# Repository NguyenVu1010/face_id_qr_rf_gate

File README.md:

# smart_gate (Pi 5 side)

See `docs/superpowers/specs/2026-05-22-pi-app-design.md` for design.

## Dev setup

```
python3 -m venv --system-site-packages .venv
source .venv/bin/activate
pip install -r requirements-dev.txt
pytest tests/ -q
```

## Production install

```
sudo bash scripts/install.sh
```

## Pi GPIO UART setup (one-time, before first run)

The daemon talks to ESP32 over the Pi GPIO UART (`/dev/serial0`), not USB-CDC.
Before first run:

1. Disable Pi serial console:
   ```
   sudo raspi-config
   # Interface Options → Serial Port
   #   "Login shell over serial?" → NO
   #   "Serial port hardware enabled?" → YES
   sudo reboot
   ```
2. Verify the device exists and is readable:
   ```
   ls -l /dev/serial0    # should be a symlink to ttyAMA0 or ttyS0
   ```
3. Wire 3 Dupont leads between Pi GPIO header and ESP32 DevKit:
   - Pi pin **8** (BCM14, TX0) → ESP32 **GPIO 32** (UART1 RX)
   - Pi pin **10** (BCM15, RX0) ← ESP32 **GPIO 25** (UART1 TX)
   - Pi pin **6** (GND) ↔ ESP32 GND

4. Add the daemon user to `dialout` so it can open `/dev/serial0`:
   ```
   sudo usermod -aG dialout smart-gate
   ```

## Flashing ESP32 (must stop daemon)

Firmware flashing still needs a separate USB cable from the Pi to the DevKit
USB-C/micro-USB port. `esptool.py` needs DTR/RTS auto-reset which the GPIO
UART doesn't provide.

```
sudo systemctl stop smart-gate
# Plug USB cable Pi → DevKit (data + power OK while daemon is stopped; the
# servo isn't moving and Pi USB current budget is plenty for the no-load case)
esptool.py --chip esp32 --port /dev/ttyUSB0 --baud 921600 write_flash 0x0 firmware.bin
# Unplug USB cable (or leave it for `pio device monitor` debug log)
sudo systemctl start smart-gate
```

After flashing, runtime traffic resumes over `/dev/serial0` (the GPIO UART).
The USB cable is optional while the daemon runs.

## Web admin smoke test (pre-merge)

With the daemon running and the ESP32 connected:

1. Open `http://<pi>:8080/`. Top bar shows green **LINK** pill + cap fps number + frame-age (< 1s). Stream `` shows a placeholder until the camera publishes.
2. Click **⏵ Open gate** — gate opens, toast "Gate opening…". Click **⏹ Close gate** — toast "Gate closing…".
3. Click **+ Tạo user mới** → confirm dialog → enroll-result card appears with QR thumbnail + ⬇ Tải QR PNG button.
4. Trigger an authorized face match — within 2 s a new row appears at the top of Recent events.
5. Watch the gate badge cycle through `idle → opening → open → timeout_warn → closing → idle` over a 20s arc; `timeout_warn` should pulse.
6. Navigate to `/events`. Toggle the `face` filter pill — only face rows show. Clear filter, choose **denied** — only stranger rows show. Type "ali" in the user search — only alice rows. Pick "Last 7 days" period. Click `▶` on a row that has a clip — native `<dialog>` modal plays the mp4 + offers Download.
7. Navigate to `/users` — alice row visible with QR thumbnail + ⬇ download button. Counter shows "N enrolled".
8. Navigate to `/system` — four status cards green (LINK / CAP / DET / DISK), pretty-printed health JSON, two diag buttons. Click **Send ping** → modal opens with `ack_ms` integer. Click **Send cmd:status** → modal updates with the ESP32-side status payload. ESP32 log scrolls live, newest-first.
9. **Failure-mode walk:**
   - Unplug USB to ESP32. Within ~5 s:
     - Top bar LINK pill turns amber.
     - `link-banner` appears: "⚠ Link down — UART silent. Manual gate commands disabled."
     - `Open gate` → toast "Gate command failed".
     - `#sse-status` becomes "reconnecting…".
   - Replug USB. Within ~5 s: banner disappears, LINK turns green, SSE pill goes live; any ESP32 log lines emitted during the outage are replayed (uses `Last-Event-ID` resume).
10. **Pause / Clear** controls on the ESP32 log list work; capacity is bounded at 500 lines (oldest dropped).

If any step fails: `pytest tests/ -q --ignore=tests/unit/test_cli.py` should still be green; the bug is in templates/JS rather than backend.

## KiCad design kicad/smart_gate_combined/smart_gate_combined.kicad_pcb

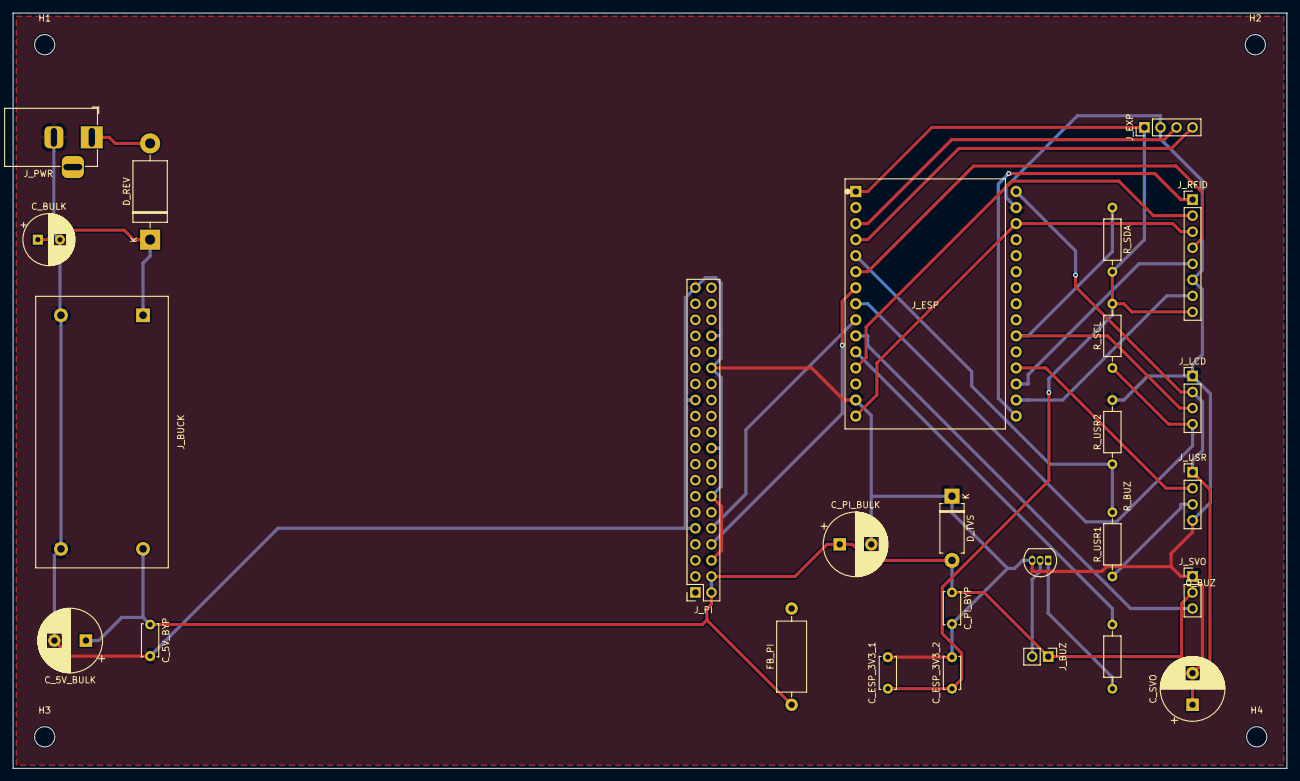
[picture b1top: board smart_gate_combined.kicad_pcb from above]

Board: 2 copper layers, 201.7 x 119.6 mm, 31 parts (0 on the bottom side), 24 nets.

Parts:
C_5V_BULK: 1000uF/10V; CP_Radial_D10.0mm_P5.00mm
C_5V_BYP: 100nF; C_Disc_D5.0mm_W2.5mm_P5.00mm
C_BULK: 100uF/25V; CP_Radial_D8.0mm_P3.50mm
C_ESP_3V3_1: 100nF; C_Disc_D5.0mm_W2.5mm_P5.00mm
C_ESP_3V3_2: 10uF; C_Disc_D5.0mm_W2.5mm_P5.00mm
C_PI_BULK: 1000uF/10V; CP_Radial_D10.0mm_P5.00mm
C_PI_BYP: 100nF; C_Disc_D5.0mm_W2.5mm_P5.00mm
C_SVO: 470uF/16V; CP_Radial_D10.0mm_P5.00mm
D_REV: 1N5817; D_DO-201AD_P15.24mm_Horizontal
D_TVS: SMAJ5.0A; D_DO-15_P10.16mm_Horizontal
FB_PI: FB_600R_3A; L_Axial_L11.0mm_D4.5mm_P15.24mm_Horizontal_Fastron_MECC
H1, H2, H3, H4: MountingHole_3.2mm_M3
J_BUCK: LM2596_Mini_Buck
J_BUZ: Buzzer_Active; PinHeader_1x02_P2.54mm_Vertical
J_ESP: ESP32_DevKit_V1; ESP32_DevKit_V1_30pin
J_EXP: Expansion; PinHeader_1x04_P2.54mm_Vertical
J_LCD: LCD_20x4_I2C; PinHeader_1x04_P2.54mm_Vertical
J_PI: Pi_5_GPIO_2x20; PinSocket_2x20_P2.54mm_Vertical
J_PWR: 12V_IN; BarrelJack_Horizontal
J_RFID: RC522; PinHeader_1x08_P2.54mm_Vertical
J_SVO: Servo_SG90; PinHeader_1x03_P2.54mm_Vertical
J_USR: HC-SR04; PinHeader_1x04_P2.54mm_Vertical
Q_BUZ: 2N3904; TO-92_Inline
R_BUZ: 1k; R_Axial_DIN0207_L6.3mm_D2.5mm_P10.16mm_Horizontal
R_SCL: 4.7k; R_Axial_DIN0207_L6.3mm_D2.5mm_P10.16mm_Horizontal
R_SDA: 4.7k; R_Axial_DIN0207_L6.3mm_D2.5mm_P10.16mm_Horizontal
R_USR1: 1k; R_Axial_DIN0207_L6.3mm_D2.5mm_P10.16mm_Horizontal
R_USR2: 2k; R_Axial_DIN0207_L6.3mm_D2.5mm_P10.16mm_Horizontal

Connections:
+3V3: C_ESP_3V3_1.1, C_ESP_3V3_2.1, J_ESP.1, J_EXP.1, J_RFID.8, R_SCL.2, R_SDA.2
+5V: C_5V_BULK.1, C_5V_BYP.1, C_PI_BULK.1, C_PI_BYP.1, C_SVO.1, D_TVS.2, FB_PI.1, J_BUCK.4, J_BUZ.1, J_ESP.2, J_LCD.2, J_PI.2, J_PI.4, J_SVO.2, J_USR.1
+12V: C_BULK.1, D_REV.1, J_BUCK.1
BUZ_COLLECTOR: J_BUZ.2, Q_BUZ.2
BUZ_DRIVE: J_ESP.21, R_BUZ.1
ESP_TX_PI_RX: J_ESP.17, J_PI.10
GND: C_5V_BULK.2, C_5V_BYP.2, C_BULK.2, C_ESP_3V3_1.2, C_ESP_3V3_2.2, C_PI_BULK.2, C_PI_BYP.2, C_SVO.2, D_TVS.1, J_BUCK.2, J_BUCK.3, J_ESP.4, J_ESP.27, J_EXP.2, J_LCD.1, J_PI.6, J_PI.9, J_PI.14, J_PI.20, J_PI.25, J_PI.30, J_PI.34, J_PI.39, J_PWR.2, J_RFID.6, J_SVO.1, J_USR.4, Q_BUZ.3, R_USR2.2
HCSR_ECHO_3V3: J_ESP.9, R_USR1.2, R_USR2.1
HCSR_ECHO_5V: J_USR.3, R_USR1.1
HCSR_TRIG: J_ESP.24, J_USR.2
I2C_SCL: J_ESP.15, J_LCD.4, R_SCL.1
I2C_SDA: J_ESP.20, J_LCD.3, R_SDA.1
IO36: J_ESP.5, J_EXP.3
IO39: J_ESP.7, J_EXP.4
unnamed: D_REV.2, J_PWR.1
unnamed: Q_BUZ.1, R_BUZ.2
PI_TX_ESP_RX: J_ESP.13, J_PI.8
RC522_CS: J_ESP.30, J_RFID.1
RC522_IRQ: J_ESP.26, J_RFID.5
RC522_MISO: J_ESP.11, J_RFID.4
RC522_MOSI: J_ESP.6, J_ESP.29, J_RFID.3
RC522_RST: J_ESP.28, J_RFID.7
RC522_SCK: J_ESP.23, J_RFID.2
SERVO_PWM: J_ESP.19, J_SVO.3

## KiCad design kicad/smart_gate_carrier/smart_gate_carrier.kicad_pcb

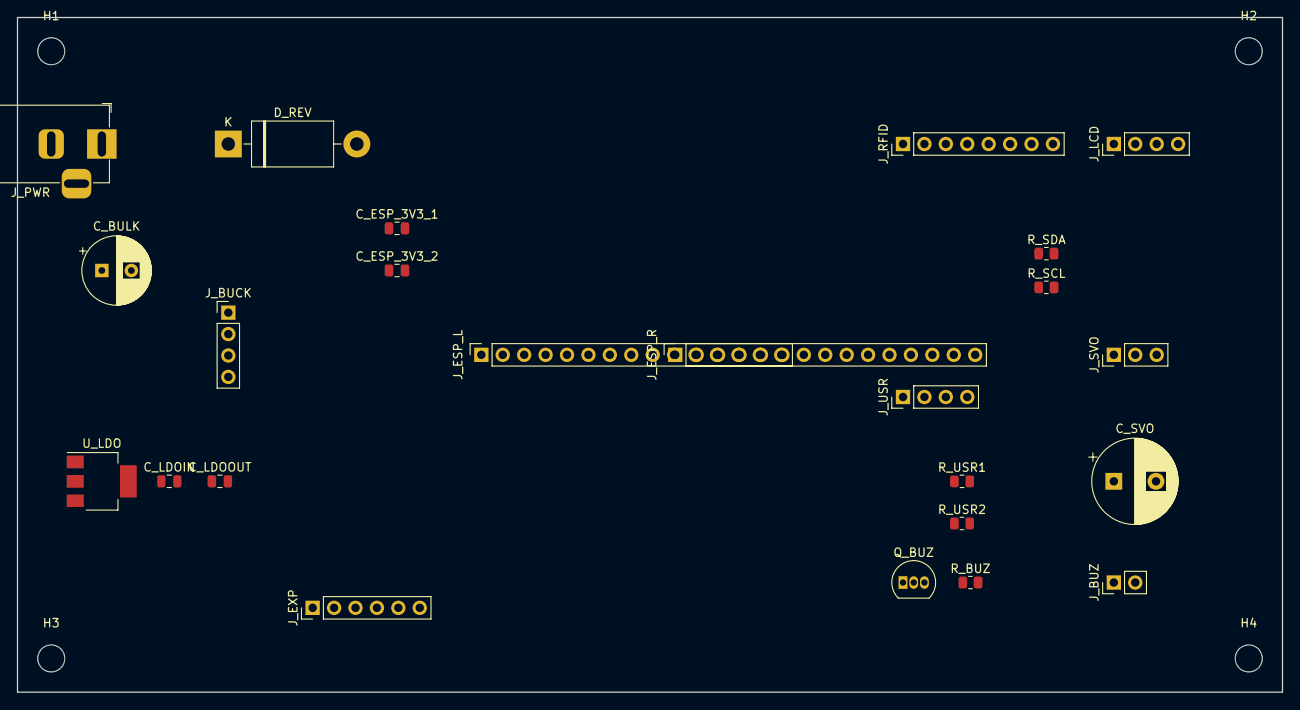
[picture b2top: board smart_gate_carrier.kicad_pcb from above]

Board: 2 copper layers, 150.0 x 80.0 mm, 28 parts (0 on the bottom side), 23 nets, no tracks yet.

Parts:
C_BULK: 100uF/25V; CP_Radial_D8.0mm_P3.50mm
C_ESP_3V3_1: 100nF; C_0805_2012Metric
C_ESP_3V3_2: 10uF; C_0805_2012Metric
C_LDOIN: 10uF; C_0805_2012Metric
C_LDOOUT: 10uF; C_0805_2012Metric
C_SVO: 470uF/16V; CP_Radial_D10.0mm_P5.00mm
D_REV: 1N5817; D_DO-201AD_P15.24mm_Horizontal
H1, H2, H3, H4: MountingHole_3.2mm_M3
J_BUCK: Buck_12V_to_5V; PinHeader_1x04_P2.54mm_Vertical
J_BUZ: Buzzer_Active; PinHeader_1x02_P2.54mm_Vertical
J_ESP_L: DevKit_L; PinSocket_1x15_P2.54mm_Vertical
J_ESP_R: DevKit_R; PinSocket_1x15_P2.54mm_Vertical
J_EXP: Expansion; PinHeader_1x06_P2.54mm_Vertical
J_LCD: LCD_20x4_I2C; PinHeader_1x04_P2.54mm_Vertical
J_PWR: 12V_IN; BarrelJack_Horizontal
J_RFID: RC522; PinHeader_1x08_P2.54mm_Vertical
J_SVO: Servo_SG90; PinHeader_1x03_P2.54mm_Vertical
J_USR: HC-SR04; PinHeader_1x04_P2.54mm_Vertical
Q_BUZ: 2N3904; TO-92_Inline
R_BUZ: 1k; R_0805_2012Metric
R_SCL: 4.7k; R_0805_2012Metric
R_SDA: 4.7k; R_0805_2012Metric
R_USR1: 1k; R_0805_2012Metric
R_USR2: 2k; R_0805_2012Metric
U_LDO: AMS1117-3.3; SOT-223-3_TabPin2

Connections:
+3V3: C_ESP_3V3_1.1, C_ESP_3V3_2.1, C_LDOOUT.1, J_ESP_L.1, J_EXP.1, J_RFID.8, R_SCL.2, R_SDA.2, U_LDO.2
+5V: C_LDOIN.1, C_SVO.1, J_BUCK.4, J_BUZ.1, J_ESP_R.1, J_LCD.2, J_SVO.2, J_USR.1, U_LDO.3
+12V: C_BULK.1, D_REV.1, D_REV.2, J_BUCK.1, J_PWR.1
BUZ_COLLECTOR: J_BUZ.2, Q_BUZ.2
BUZ_DRIVE: J_ESP_L.11, R_BUZ.1
GND: C_BULK.2, C_ESP_3V3_1.2, C_ESP_3V3_2.2, C_LDOIN.2, C_LDOOUT.2, C_SVO.2, J_BUCK.2, J_BUCK.3, J_ESP_L.14, J_ESP_R.2, J_EXP.2, J_LCD.1, J_PWR.2, J_RFID.6, J_SVO.1, J_USR.4, Q_BUZ.3, R_USR2.2, U_LDO.1
HCSR_ECHO_3V3: J_ESP_L.5, R_USR1.2, R_USR2.1
HCSR_ECHO_5V: J_USR.3, R_USR1.1
HCSR_TRIG: J_ESP_L.9, J_USR.2
I2C_SCL: J_ESP_L.8, J_LCD.4, R_SCL.1
I2C_SDA: J_ESP_L.7, J_LCD.3, R_SDA.1
IO5: J_ESP_R.15, J_EXP.4
IO17: J_ESP_R.14, J_EXP.3
IO36: J_ESP_L.3, J_EXP.5
IO39: J_ESP_L.4, J_EXP.6
unnamed: Q_BUZ.1, R_BUZ.2
RC522_CS: J_ESP_R.10, J_RFID.1
RC522_IRQ: J_ESP_R.13, J_RFID.5
RC522_MISO: J_ESP_L.6, J_RFID.4
RC522_MOSI: J_ESP_L.15, J_ESP_R.3, J_RFID.3
RC522_RST: J_ESP_R.12, J_RFID.7
RC522_SCK: J_ESP_L.12, J_RFID.2
SERVO_PWM: J_ESP_L.10, J_SVO.3

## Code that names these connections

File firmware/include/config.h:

#pragma once

// === Pin assignments (mirror architecture spec §5) ===
#define PIN_LED_STATUS   2
#define PIN_RC522_CS     5
#define PIN_RC522_SCK    18
#define PIN_RC522_MISO   19
#define PIN_RC522_MOSI   23
#define PIN_RC522_RST    17
#define PIN_RC522_IRQ    16
#define PIN_LCD_SDA      21
#define PIN_LCD_SCL      22
#define PIN_SR04_TRIG    27
#define PIN_SR04_ECHO    26
#define PIN_SERVO        13
#define PIN_BUZZER       14

// Pi link runs on ESP32 UART1 routed via the GPIO matrix (decision #26, 2026-05-23).
// Pi pin 8 (BCM14, TX0) → ESP32 GPIO 32 (UART1 RX);
// Pi pin 10 (BCM15, RX0) ← ESP32 GPIO 25 (UART1 TX).
// UART0 (GPIO 1/3, USB-CDC) stays reserved for `pio device monitor` debug + `esptool.py` flashing.
#define PIN_PI_UART_RX   32
#define PIN_PI_UART_TX   25

// === Timings (ms) ===
#define DEFAULT_OPEN_REACHED_MS    300
#define DEFAULT_CLOSE_REACHED_MS   300
#define DEFAULT_PASSAGE_TIMEOUT_MS 10000
#define DEFAULT_WARN_GIVEUP_MS     5000
#define HEARTBEAT_INTERVAL_MS      10000
#define RFID_POLL_INTERVAL_MS      50
#define SENSOR_POLL_INTERVAL_MS    50
#define SENSOR_DEBOUNCE_COUNT      3
#define SENSOR_TRIGGER_CM          25

// === Servo angles ===
#define DEFAULT_SERVO_OPEN_DEG     100
#define DEFAULT_SERVO_CLOSE_DEG    10
// Physical safe range for SG90 horn vs enclosure — protects against a bad
// cmd:config (e.g. servo_open_deg=180) driving the horn into the wall and
// stalling the motor at ~700 mA until brown-out.
#define SERVO_MIN_PHYS_DEG         5
#define SERVO_MAX_PHYS_DEG         110
// Expected servo travel time end-to-end. Used both for the async detach timer
// margin and as the base period for the stall watchdog (2× this value).
// Kept aligned with DEFAULT_OPEN_REACHED_MS / DEFAULT_CLOSE_REACHED_MS so the
// reached-event and stall windows stay consistent.
#define SERVO_EXPECTED_TRAVEL_MS   DEFAULT_OPEN_REACHED_MS

// === LCD ===
#define LCD_I2C_ADDR              0x27
#define LCD_COLS                  20
#define LCD_ROWS                  4

// === NVS ===
#define NVS_NS_ALLOWLIST          "allowlist"
#define NVS_NS_CONFIG             "config"
#define NVS_NS_GATE_STATE         "gate_state"
#define NVS_INDEX_KEY             "_index"
#define ALLOWLIST_MAX_ENTRIES     100

// === Brown-out recovery ===
// Hold servo at 90° neutral for this long before falling through to enter_idle(),
// giving any person in the doorway time to step clear.
#define RECOVERY_HOLD_MS          5000
#define RECOVERY_NEUTRAL_DEG      90

// === UART / JSON ===
#define UART_BAUD                 115200
#define UART_LINE_MAX             512
#define JSON_DOC_CAPACITY         768
#define EVENT_QUEUE_LEN           16
#define OUTBOUND_QUEUE_LEN        16

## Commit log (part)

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2026-05-21 docs: add ESP32 firmware design spec and implementation plan
    Spec describes the four-task FreeRTOS architecture (uart_link, rfid,
    sensor, gate_fsm), Arduino-ESP32 + PlatformIO toolchain choice, NVS
    allowlist schema, and 12 manual acceptance scenarios.
    Plan breaks delivery into 12 bite-sized tasks, each ending in a
    compile-clean state and a git commit.
2026-05-22 feat(firmware): bootstrap PlatformIO project skeleton
2026-05-22 docs(firmware): pin emit_log signature and clarify event struct comments
    Per code review on Task 1: log.h now states the expected emit_log signature
    so Task 4 cannot silently introduce a contract mismatch. events.h adds notes
    about uid[] sizing assumption and outbound_msg_t newline policy.
2026-05-22 feat(firmware): add NVS-backed RFID allowlist module
2026-05-22 scaffold: project layout, deps, pytest
2026-05-22 scaffold: test fixtures dir + tmp_data_dir helper
2026-05-22 feat(firmware): add inline drivers (servo, LCD, buzzer)
2026-05-22 config: TOML loader with nested dataclasses + defaults
2026-05-22 data: SQLite migrations + Database connection helper
    Adds smart_gate.data package with:
    - 0001_init.sql migration defining users, face_encodings, qr_tokens,
    events, esp_log, _meta tables with WAL + foreign keys, cascade
    deletes, ON DELETE SET NULL on events, and a partial unique index
    ensuring at most one active QR token per user.
    - Database helper providing per-thread connections, autocommit mode,
2026-05-22 feat(firmware): add uart_link JSON Lines RX/TX module
2026-05-22 data: query methods + dataclass models
2026-05-22 fix(firmware): null-guard outbound_q in uart_link TX drain
    Same defensive pattern as outbound_post/outbound_send. Prevents a crash if
    task creation order in Task 9 ever changes such that uart_link_task starts
    before g_outbound_q is initialized.
2026-05-22 feat(firmware): add MFRC522 RFID polling task
2026-05-22 link: protocol encode/decode (JSON Lines, MAX_LINE 512)
2026-05-22 feat(firmware): add HC-SR04 passage sensor task
2026-05-22 video: FrameHub Condition-based fan-out
2026-05-22 video: FrameHub per-channel TLS tracking
    Track last_seen seq per (thread, channel) pair so calling wait_jpeg() then
    wait_bgr() on the same thread doesn't deadlock the second call. Fixes the
    spin-on-cached-frame bug while satisfying all 4 tests including the
    same-thread sequential read in test_publish_then_wait_returns_latest.
2026-05-22 video: recorder cleanup_pass (retention E: age OR size)
2026-05-22 feat(firmware): wire up boot sequence and FreeRTOS tasks
2026-05-22 video: RingBuffer + recorder thread + ffmpeg invocation
2026-05-22 docs(firmware): pin map, build/flash, and acceptance tests
2026-05-22 link: UartClient (rx/tx/heartbeat, reconnect, ack tracking)
2026-05-22 recognition: detector thread (MediaPipe + face_recognition + pyzbar)
2026-05-22 web: Flask app factory, routes, templates
2026-05-22 cli: argparse dispatcher + enroll/qr/users/events subcommands
2026-05-22 packaging: systemd unit + install.sh
2026-05-22 chore(kicad): remove stray smart_gate_carrier folder (recreated by KiCad open-recent)
2026-05-22 feat(firmware): switch Pi link from USB-CDC to GPIO UART1 (decision #26)
    Runtime Pi↔ESP32 app comm now uses ESP32 UART1 on GPIO 32 (RX) / GPIO 25
    (TX), routed through the Pi GPIO header pins 8/10 (BCM14/15). UART0
    (GPIO 1/3, USB-CDC) stays exclusively for `pio device monitor` debug and
    `esptool.py` flashing.
    Architecture spec was updated 2026-05-23 on main (commits 14bf951 +
    de14c5e) but the firmware code was tagged "NOT YET APPLIED" — this
2026-05-23 fix(link): EspLogBus.unsubscribe must use object identity
    list.remove(q) used value equality; two empty deques compare equal so
    bus.unsubscribe(q1) could silently remove q2 if both were empty.
    Replace with an identity-based scan. Regression test added.
2026-05-23 plan: smart_gate enclosure (FreeCAD build script, 3 parts, STL export)
2026-05-23 feat(freecad): enclosure build script (3 parts, STL export)
    Implements docs/superpowers/specs/2026-05-23-smart-gate-enclosure-design.md
    per docs/superpowers/plans/2026-05-23-smart-gate-enclosure.md.
    build_enclosure.py is run via FreeCAD MCP (mcp__freecad__execute_code),
    not standalone Python. Idempotent — overwrites smart_gate_enclosure.FCStd
    and exports 3 STL files (box_body, connector_plate, lid) on each run.
    Geometry:
2026-05-23 fix(freecad): swap DC jack and peripheral wire walls + enlarge wire slots
    - DC jack: WEST -> EAST wall (round Ø11mm at Y=27.4, Z=14.6)
    - Peripheral wires: EAST -> WEST wall (rect 15x20mm, 4 slots)
    - Slot size: 5x10mm -> 15x20mm to fit Dupont bundles 7-10 wires
    Internal cable from PCB J_PWR (PCB-X=12.46, near west PCB edge) now
    runs ~185mm east inside the box to reach the DC jack hole on east wall.
2026-05-23 fix(freecad): reduce wire exit slot height from 20mm to 10mm
2026-05-23 feat(freecad): import motherboard PCB STEP for visual reference
2026-05-23 fix(freecad): rotate PCB 180° around Z (mirror X+Y) so J_PWR aligns with east wall DC jack cutout
2026-05-23 fix(freecad): DC jack Z position must include standoff height (z=14.6mm not 10.1mm)
2026-05-23 feat(freecad): rabbet joint (2mm ledges) for plate-box interlock
2026-05-23 fix(freecad): remove rabbet ledges; notch corner pillars at PCB level so PCB fits
2026-05-23 fix(freecad): reduce corner pillars 10mm -> 7mm to clear PCB corners (no notch needed)
2026-05-23 feat(freecad): enlarge LCD cutout to 98x40mm with R=4mm filleted corners
2026-05-30 fix(laser_cut): widen stroke (0.3 cut / 0.5 engrave) so PDF preview is readable
2026-05-30 docs(laser_cut): README for the laser shop
2026-05-30 test(laser_cut): end-to-end integration test
2026-06-13 feat(web): asset_check module — flag missing/placeholder static assets
    Catches the htmx.min.js placeholder-in-git problem at Flask boot:
    returns list of degraded asset names. I/O errors treated as degraded
    rather than raised so a misconfigured permission can't crash startup.
2026-06-13 feat(web): degraded-asset banner in base.html + sticky-top style
    Banner renders on every page when app.config['ASSET_WARNINGS'] is
    non-empty so admin sees the problem immediately on any route.
2026-06-13 fix(web): drop sticky from asset-warning banner
    Two siblings at position:sticky top:0 collided - banner z-index 10000
    covered .topbar (z-index 10) on scroll, making nav links unclickable.
    Banner is loud enough on initial render; scrolling it away with content
    lets the topbar stay usable. Per code review on c950915.
2026-06-13 docs(spec): RFID auto-fill UID in Add-user modal
    Client-only change: while the Add-user modal is open in RFID mode,
    listen to /api/esp_log/stream, regex-extract uid=… from rfid-tagged
    log lines, write into the input + brief green border flash. No backend
    changes — denial audit log already carries the UID.
2026-06-13 docs(plan): RFID auto-fill UID — 2-task client-only plan
    Implements 2026-06-13-rfid-auto-fill-uid-design.md. Task 1: extend the
    Add-user modal IIFE with a mode-scoped EventSource that regex-extracts
    uid=… from rfid-tagged SSE log events into the input + flash CSS, plus
    syntax/regression checks. Task 2: deploy to /opt/smart-gate + 5-step
    lifecycle manual verification covering positive, switch-out, close,
    submit-finally, and negative paths.
2026-06-13 docs(spec): RFID user-management overhaul — 4 features in one sweep
    Consolidates four related gaps into one coherent feature branch:
    1. Auto-fill UID in Add-user modal (folds in prior auto-fill spec)
    2. Modal RFID mode supports binding to existing user (dropdown)
    3. /users page lists each user's UIDs with × remove buttons
    4. DELETE /api/users/<name> cascades cmd:remove_uid for all bound UIDs
    (closes security gap where deleted users' cards still opened the gate)
2026-06-13 docs(plan): RFID user-management overhaul — 6-task TDD plan
    Implements 2026-06-13-rfid-user-management-design.md. Task 1: shared
    _list_uids_for_user helper + 5 tests. Task 2: GET /api/users/<name>/rfid.json
    + 3 tests. Task 3: cascade cmd:remove_uid in DELETE /api/users/<name> +
    3 tests. Task 4: dashboard modal — auto-fill UID + target picker
    (new vs existing user). Task 5: /users page chip list with × remove.
    Task 6: deploy to /opt/smart-gate + 7 manual checks.
2026-06-13 feat(web): _list_uids_for_user helper — Pi-side filter of cmd:list_uids
    Single shared call site for both the per-user UID list endpoint and
    the delete-user cascade. LinkDown/timeout/malformed payload all return
    [] so callers don't repeat defensive parsing. 5 TDD unit tests cover
    the happy path + three failure modes + None uart.
2026-06-13 feat(web): Add-user modal — auto-fill UID + bind to existing user
    Modal RFID mode grows two capabilities:
    1. SSE listener (mode-scoped) extracts uid=… from rfid log lines and
    populates the input with a brief green flash. EventSource opened on
    mode-into-RFID, closed on mode-out / cancel / dialog close /
    submit-finally.
    2. Radio above the UID field: 'Tạo user mới' (default) or 'Bind vào
2026-06-13 feat(web): /users page — UID chips with × remove per user
    Each user row fetches /api/users/<name>/rfid.json on load and renders
    one .uid-chip per bound UID. × button confirms then DELETEs via the
    existing /api/users/<name>/rfid/<uid> route, removing the chip on
    success. 'chưa có thẻ' placeholder for users with no UIDs.
2026-06-13 fix(web): dropdown handles /api/users.json flat-array response
    The endpoint returns a JSON array (not {users:[...]}) so the previous
    extraction (j && j.users) silently produced [] and the dropdown stayed
    empty. Accept both shapes: Array.isArray(j) ? j : (j.users || []).
    Caught during Task 6 deployment verification.
2026-06-19 feat(firmware): LCD shows Vietnamese (ASCII) idle/grant/deny messages
    Idle screen now reads "Xin moi quet:" with Khuon mat / QR code / The chip RFID
    on rows 1-3. Grant shows "Xin moi vao" (+ name on row 2 when known); deny shows
    "Vui long thu lai". HD44780 has no diacritic glyphs, so accents are stripped —
    warn/closing/recovery keep their existing English text.
2026-06-19 fix(web): unwrap UART ack correctly + renumber STT on /users delete
    UartClient.send_cmd already unwraps the ack envelope and returns the inner
    `data` dict, so _list_uids_for_user and the DELETE cascade must not unwrap
    again. The double-unwrap silently returned empty for every user, breaking
    both the UID chip display and the cmd:remove_uid cascade — re-opening the
    security gap that 0d67ddd was meant to close. Tests had the same bug in
    their mock helper, so they kept passing against the broken code; fixed the
2026-06-19 chore: drop build artifacts, archived PCB v1, and stale exports
    Removes generated outputs that re-emit from source:
    - kicad/smart_gate_combined/*.svg|.dsn|.ses|.erc|drc_report.txt (build_combined.py)
    - kicad/archive/smart_gate_carrier_v1_esp32only/ (PCB v1, pre-respin 2026-06-05; in git history)
    - freecad/exports/, 3d/, doc/requirement.txt
    Moves the prototype BOM into doc/ and extends .gitignore so future
    KiCad/FreeCAD/PlatformIO output never lands in tree again.
